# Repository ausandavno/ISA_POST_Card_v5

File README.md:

# ISA_POST_Card_v5
A plug-in diagnostic card that displays Power On Self Test (POST) codes on an 8-bit ISA data bus. Tested for use with Micro8088 and Xi8088 systems. Can be configured to listen on any address in the lower ten bits of address space. 

Current version v5.1

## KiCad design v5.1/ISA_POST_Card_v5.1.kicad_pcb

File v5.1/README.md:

# ISA_POST_Card_v5.1
Version 5.1 of a plug-in diagnostic card that displays Power On Self Test (POST) codes on an 8-bit ISA data bus. Tested for use with Micro8088 and Xi8088 systems. Can be configured to listen on any address in the lower ten bits of address space.

Board render:

Constructed board (ignore version number):

## Hardware Documentation

### Schematic and PCB Layout

[Schematics - Version 5.1 (pdf)](../v5.1/Schematics/ISA_POST_Card_v5.1-Schematic.pdf)

[PCB Layout - Version 5.1 (zip)](../v5.1/PCB_Layout/ISA_POST_Card_v5.1-PCB_Layouts.zip)

[Gerbers - Version 5.1 (zip)](../v5.1/Gerbers/ISA_POST_Card_v5.1-Gerbers.zip)

### Building Instructions

Recommend soldering components in order of height, lowest to highest: Resistors (Rx), IC sockets (if used), Resistor Networks (RNx), Capacitors (Cx), Discrete LEDs (Dx), Seven Segment LEDs (LEDx), Switches (SWx).

Recommend populating turned-pin strip headers for U2, U3, U9 and U10. Populate U2, U3 if intending to use seven-segment display driver 74LS47. Populate U9, U10 if intending to use ATF16V8B-15PU to display hexadecimal values.

### Jumpers and Switches

#### JP1 - Select chip options for U1
Position | Description
-------- | -----------
1-2 closed (default)* | Use 74x273 Series
2-3 closed | Use 74x374 Series

*Cut trace to open 1-2

#### SW1 - Lowest five bits of address space selection
Position	| Description
-------- | -----------
SW1.1 | bit 4 of address space
SW1.2 | bit 3 of address space
SW1.3 | bit 2 of address space
SW1.4 | bit 1 of address space
SW1.5 | bit 0 of address space (LSB)

#### SW2 - Highest five bits of address space selection
Position	| Description
-------- | -----------
SW2.1 | bit 9 of address space (MSB)
SW2.2 | bit 8 of address space
SW2.3 | bit 7 of address space
SW2.4 | bit 6 of address space
SW2.5 | bit 5 of address space

### Bill of Materials - v5.1

Component type     | Reference | Description            | Quantity | Possible sources and notes 
------------------ | --------- | ---------------------- | -------- | --------------------------
PCB                |           | ISA Post Card v5.1     | 1        | Use supplied Gerber or KiCad files to order from your perferred PCB fabrication house
Integrated Circuit | U1        | 74ALS273 or 74ALS374 (See JP1 Setting)   | 1        | Mouser [SN74ALS273N](https://www.mouser.com/ProductDetail/595-SN74ALS273N) or [SN74ALS374AN](https://www.mouser.com/ProductDetail/595-SN74ALS374AN)
Integrated Circuit | U2, U3    | 74LS47 (Alternative to U9, U10)   | 2        | Mouser [SN74LS47NE4](https://www.mouser.com/ProductDetail/595-SN74LS47NE4)
Integrated Circuit | U4, U5    | 74ALS521 or 74HCT688   | 2        | Mouser [SN74ALS521N](https://www.mouser.com/ProductDetail/595-SN74ALS521N) or [CD74HCT688E](https://www.mouser.com/ProductDetail/595-CD74HCT688E)
Integrated Circuit | U6, U7    | 74HCT132                | 2        | Mouser [CD74HCT132E](https://www.mouser.com/ProductDetail/595-CD74HCT132E)
Integrated Circuit | U8        | 74LS74                 | 1        | Mouser [SN74LS74AN](https://www.mouser.com/ProductDetail/595-SN74LS74AN)
Integrated Circuit | U9, U10   | ATF16V8B (Alternative to U2, U3) | 2        | Mouser [ATF16V8B-15PU](https://www.mouser.com/ProductDetail/556-AF16V8B15PU)
LED    | LED1, LED2   | 7-Segment Display W7.4mm H10mm  | 2        | Mouser [LTS-2801AG](https://www.mouser.com/ProductDetail/859-LTS-2801AG) or [LTS-2801AWC](https://www.mouser.com/ProductDetail/859-LTS-2801AWC)
LED | D1 - D4   | LED D3.0mm    | 4        | Mouser [LTL-4231N](https://www.mouser.com/ProductDetail/859-LTL-4231N)
Resistor Network   | RN1, RN2  | R_Array_SIP6 10K (Bussed)      | 2   | Mouser [4606M-101-103LF](https://www.mouser.com/ProductDetail/652-4606M-1LF-10K)
Resistor Network   | RN3 - RN6  | R_Array_SIP8 1K (Isolated)   | 4  |  Mouser [L083S122LF](https://www.mouser.com/ProductDetail/858-L083S122LF)
Resistor   | R1  | R_Axial_DIN0207 L6.3mm D2.5mm P10.16mm 10K       | 1        | Mouser [MFR-25FRF52-10K](https://www.mouser.com/ProductDetail/603-MFR-25FRF5210K)
Resistor   | R9, R13  | R_Axial_DIN0207 L6.3mm D2.5mm P10.16mm 1k | 2 | Mouser [MFR-25FRF52-1K](https://www.mouser.com/ProductDetail/MFR-25FRF52-1K)
Resistor   | R10, R14  | R_Axial_DIN0207 L6.3mm D2.5mm P10.16mm 2.4k | 2 | Mouser [MFR-25FRF52-2K4](https://www.mouser.com/ProductDetail/603-MFR-25FRF52-2K4)
Capacitor   | C1 - C8  | P5.08mm 0.1uF 50V  | 8        | Mouser [FG28X7R1H104KNT06](https://www.mouser.com/ProductDetail/810-FG28X7R1H104KNT6)
Capacitor   | C9  | P5.08mm 10uF 10V  | 1        | Mouser [FG24X7R1A106KRT06](https://www.mouser.com/ProductDetail/810-FG24X7R1A106KRT6)
Switch   | SW1, SW2  | SW_DIP_SPSTx05_Slide 9.78x14.88mm W7.62mm P2.54mm   | 2    | Mouser [CTS 206-5](https://www.mouser.com/ProductDetail/774-2065) or [C&K BD05](https://www.mouser.com/ProductDetail/611-BD05)
Socket   | for U1, U4, U5 | 20 pin 300 mil DIP socket    | 3    | Mouser [4820-3000-CP](https://www.mouser.com/ProductDetail/517-4820-3000-CP)
Socket   | for U6, U7, U8 | 14 pin 300 mil DIP socket    | 3    | Mouser [4814-3000-CP](https://www.mouser.com/ProductDetail/517-4814-3000-CP)
Socket *   | for U9, U10 | 10 WAY SIL VERT SKT           | 4    | Mouser [D01-9971042](https://www.mouser.com/ProductDetail/855-D01-9971042)
Socket *   | for U2, U3 | 8 WAY SIL VERT SKT            | 4    | Mouser [D01-9970842](https://www.mouser.com/ProductDetail/855-D01-9970842)
Socket **   | Alt for U9, U10 | 20 pin 300 mil DIP socket  | 2    | Mouser [4820-3000-CP](https://www.mouser.com/ProductDetail/517-4820-3000-CP)
Socket **   | Alt for U2, U3 | 16 pin 300 mil DIP socket   | 2    | Mouser [4816-3000-CP](https://www.mouser.com/ProductDetail/517-4816-3000-CP)

*Recommended to use SIL Sockets instead of DIP sockets if you want to swap between fitting U2, U3 and U9, U10.

**Use DIP sockets if you are comfortable committing to either U2, U3 or U9, U10. Cannot swap between chip types without removing DIP socket. 

### Alternative ICs

Supply chain distruptions have caused havoc with availability of ICs. Below are some suggestions for alternative types that are likely to work as substitues to those in the BOM. NOTE: not all alternative chip types or combinations of chip types have been tested. Use caution substituting CMOS types for Bipolar types. Bipolar outputs to CMOS inputs may give issues with voltage levels.

* 74ALS273 Alternatives:
  * Mouser [SN74LS273N](https://www.mouser.com/ProductDetail/595-SN74LS273N)
  * Mouser [SN74HCT273N](https://www.mouser.com/ProductDetail/595-SN74HCT273N)
  * Mouser [CD74ACT273E](https://www.mouser.com/ProductDetail/595-CD74ACT273E)

* 74ALS374 Alternatives:
  * Mouser [SN74LS374N](https://www.mouser.com/ProductDetail/595-SN74LS374N)
  * Mouser [SN74F374N](https://www.mouser.com/ProductDetail/595-SN74F374N)
  * Mouser [SN74HCT374N](https://www.mouser.com/ProductDetail/595-SN74HCT374N)
  * Mouser [CD74ACT374E](https://www.mouser.com/ProductDetail/595-CD74ACT374E)

* 74ALS521 Alternatives:
  * Mouser [SN74F521N](https://www.mouser.com/ProductDetail/595-SN74F521N)

* 74HCT688 Alternatives:
  * Mouser [SN74LS688N](https://www.mouser.com/ProductDetail/595-SN74LS688N)
  * Mouser [SN74ALS688N](https://www.mouser.com/ProductDetail/595-SN74ALS688N)

* 74HCT132 Alternatives:
  * Mouser [SN74LS132N](https://www.mouser.com/ProductDetail/595-SN74LS132N)

* 74LS74 Alternatives:
  * Mouser [SN74ALS74AN](https://www.mouser.com/ProductDetail/595-SN74ALS74AN)
  * Mouser [SN74F74N](https://www.mouser.com/ProductDetail/595-SN74F74N)
  * Mouser [CD74HCT74E](https://www.mouser.com/ProductDetail/595-CD74HCT74E)
  * Mouser [CD74ACT74E](https://www.mouser.com/ProductDetail/595-CD74ACT74E)

## Firmware Documentation

### ATF16V8B

The ATF16V8B-15PU chip (U9, U10) can be chosen as a substitute to the 74LS47 (U2, U3). The ATF16V8B chip is primarily used to emulate a 74LS47 seven segment display decoder IC with additional/new hex-output functionality. If one would like to be able to see hexadecimal values on the seven-segment displays of the POST card, then the ATF16V8B should be chosen.

The ATF16V8B must be programmed with a ".jed" file. A copy of this file "HEX_TO_7SEG_DECODER_COM_AN_V2.0.jed" has been placed in the "ATF16V8B_JED" folder.

Refer to my [Hex_To_Seven_Segment_Decoder](https://github.com/ausandavno/Hex_To_Seven_Segment_Decoder/tree/master/COMMON_ANODE_v2.0) repository for associated WinCUPL project files.

Refer to [My website](https://www.andavno.com/?p=672) for an overview of recent changes to the ATF16V8B program.

For some instruction on how to compile the WinCUPL code for the ATF16V8B, please see “How to Compile the Code” section of my post [7 segment display decoder with HEX output](https://www.andavno.com/?p=539).

For some instruction on how to go about programming the ATF16V8B with a TL866II PLUS programmer, please see “Flashing U16” section of my post on [building the Micro 8088](https://www.andavno.com/?p=85).

## Changes
* Version 5.1
  * First Issue

## Known Issues
* Version 5.1
  * None at present
 
## Open Hardware License
 
You may redistribute and modify this Covered Source, and make products using it, under the terms of the CERN-OHL-P v2 (https:/cern.ch/cern-ohl). This Covered Source is distributed WITHOUT ANY EXPRESS OR IMPLIED WARRANTY, INCLUDING OF MERCHANTABILITY, SATISFACTORY QUALITY AND FITNESS FOR A PARTICULAR PURPOSE. Please see the CERN-OHL-P v2 for applicable conditions.
 
Warranty Disclaimed per 5.1 of CERN-OHL-P v2.
 
Liability Excluded and Limited per 5.2 of CERN-OHL-P v2.
 
See "LICENSE_NOTICES_and_CHANGES.txt" for specific Notices relating to this hardware design.

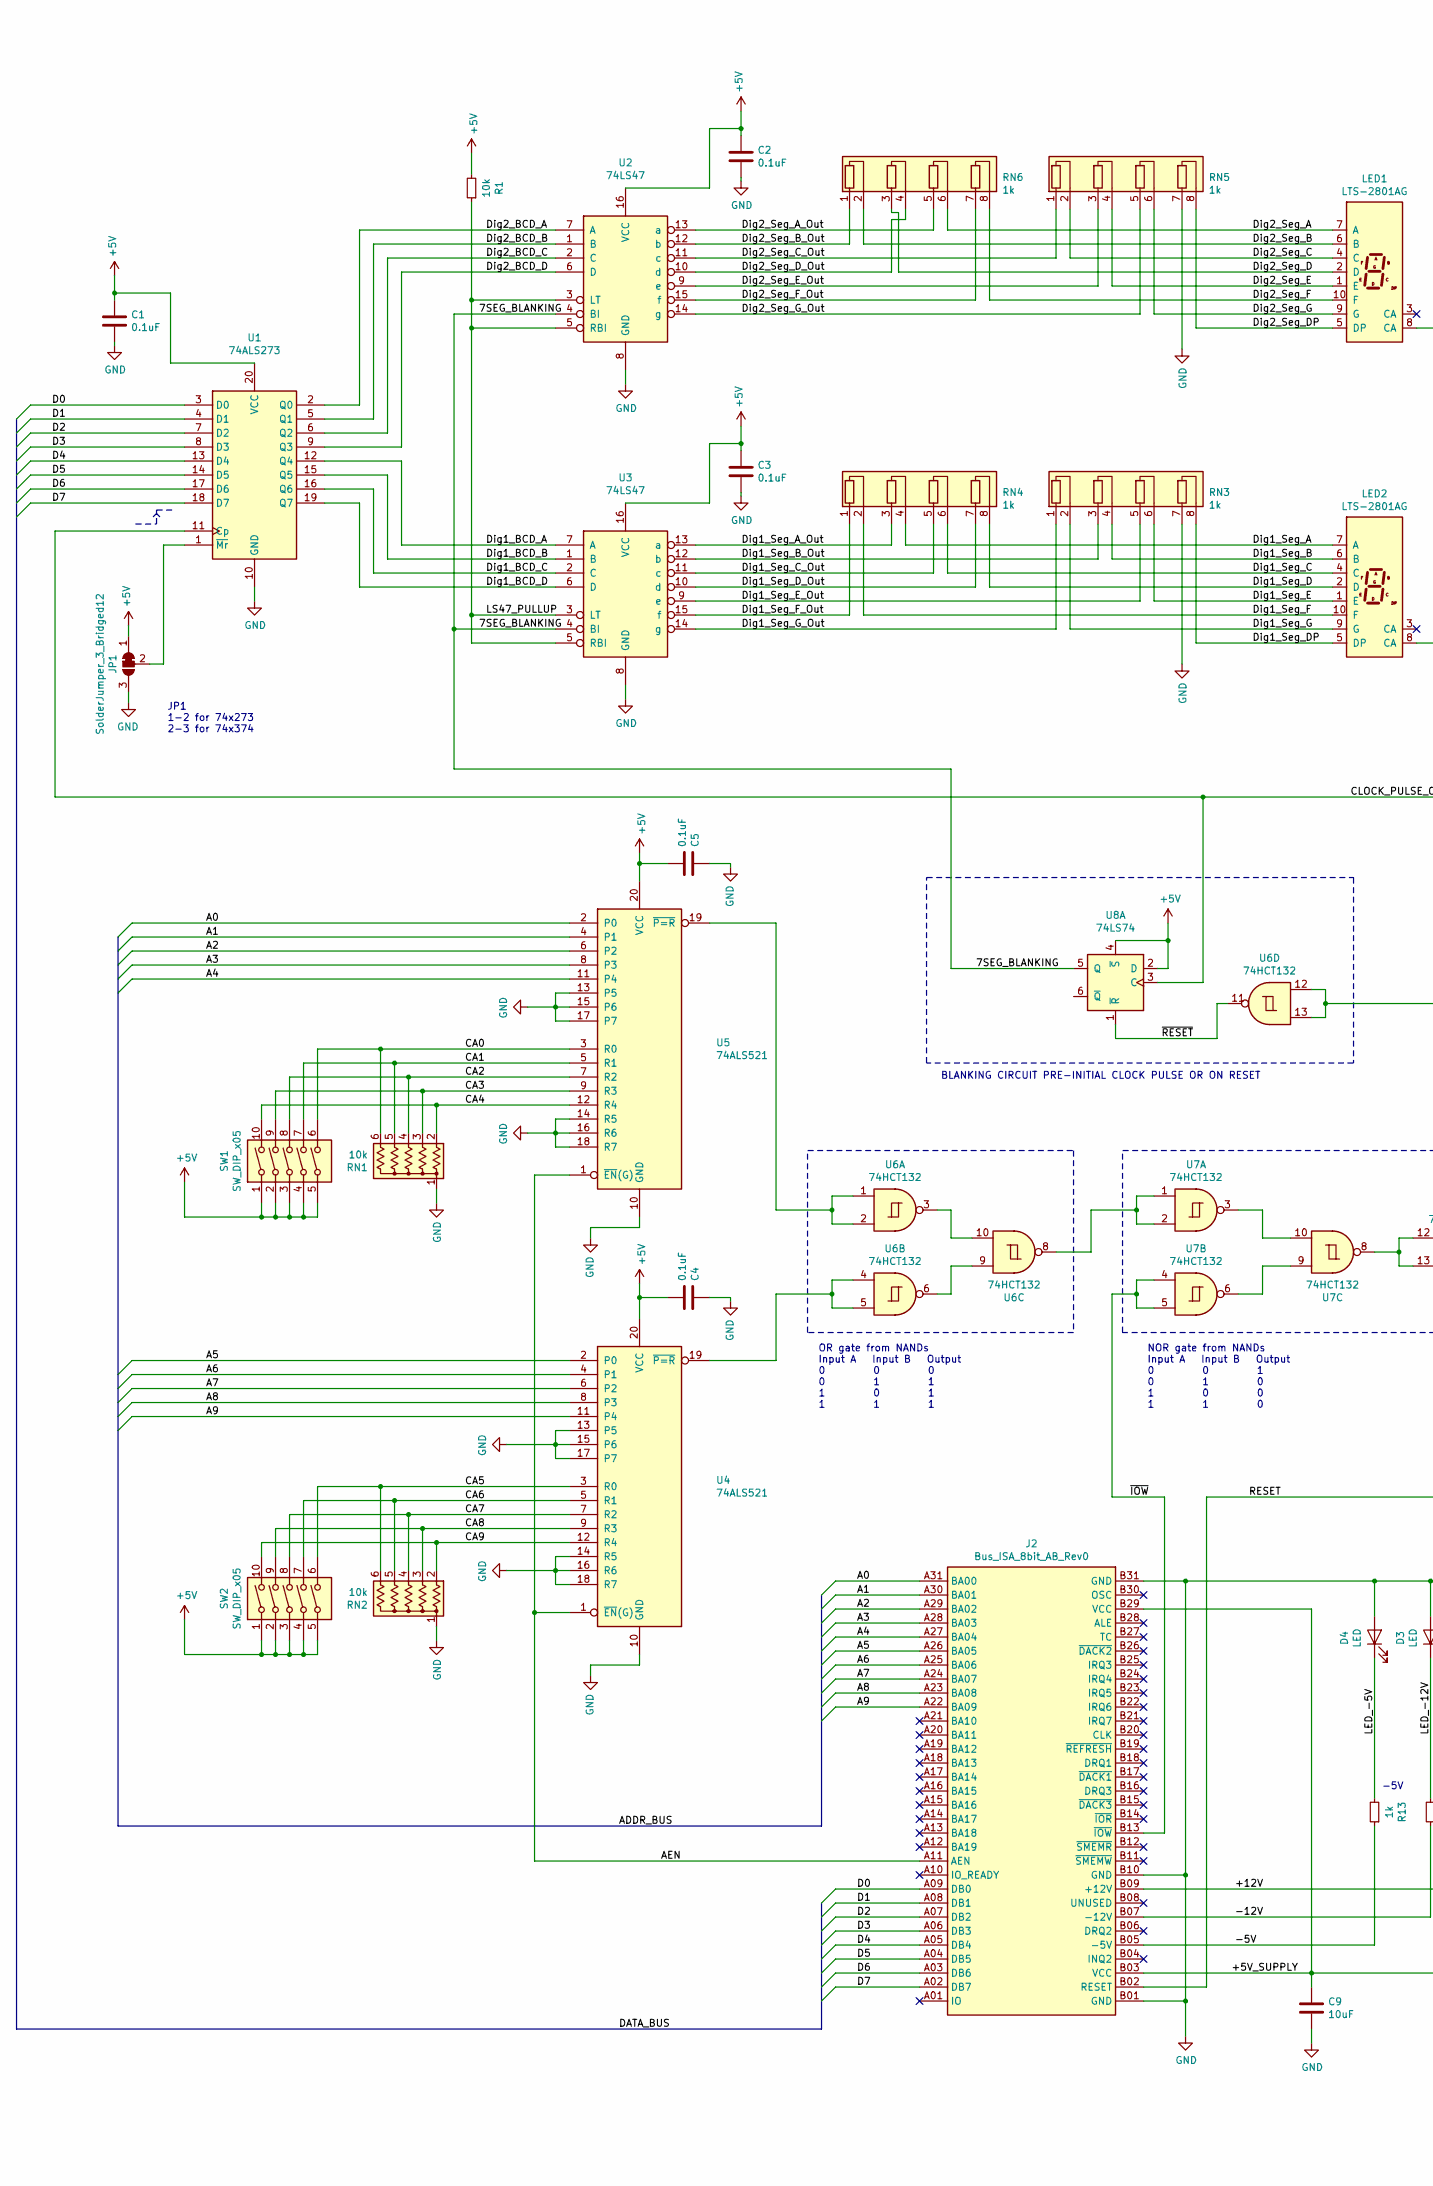
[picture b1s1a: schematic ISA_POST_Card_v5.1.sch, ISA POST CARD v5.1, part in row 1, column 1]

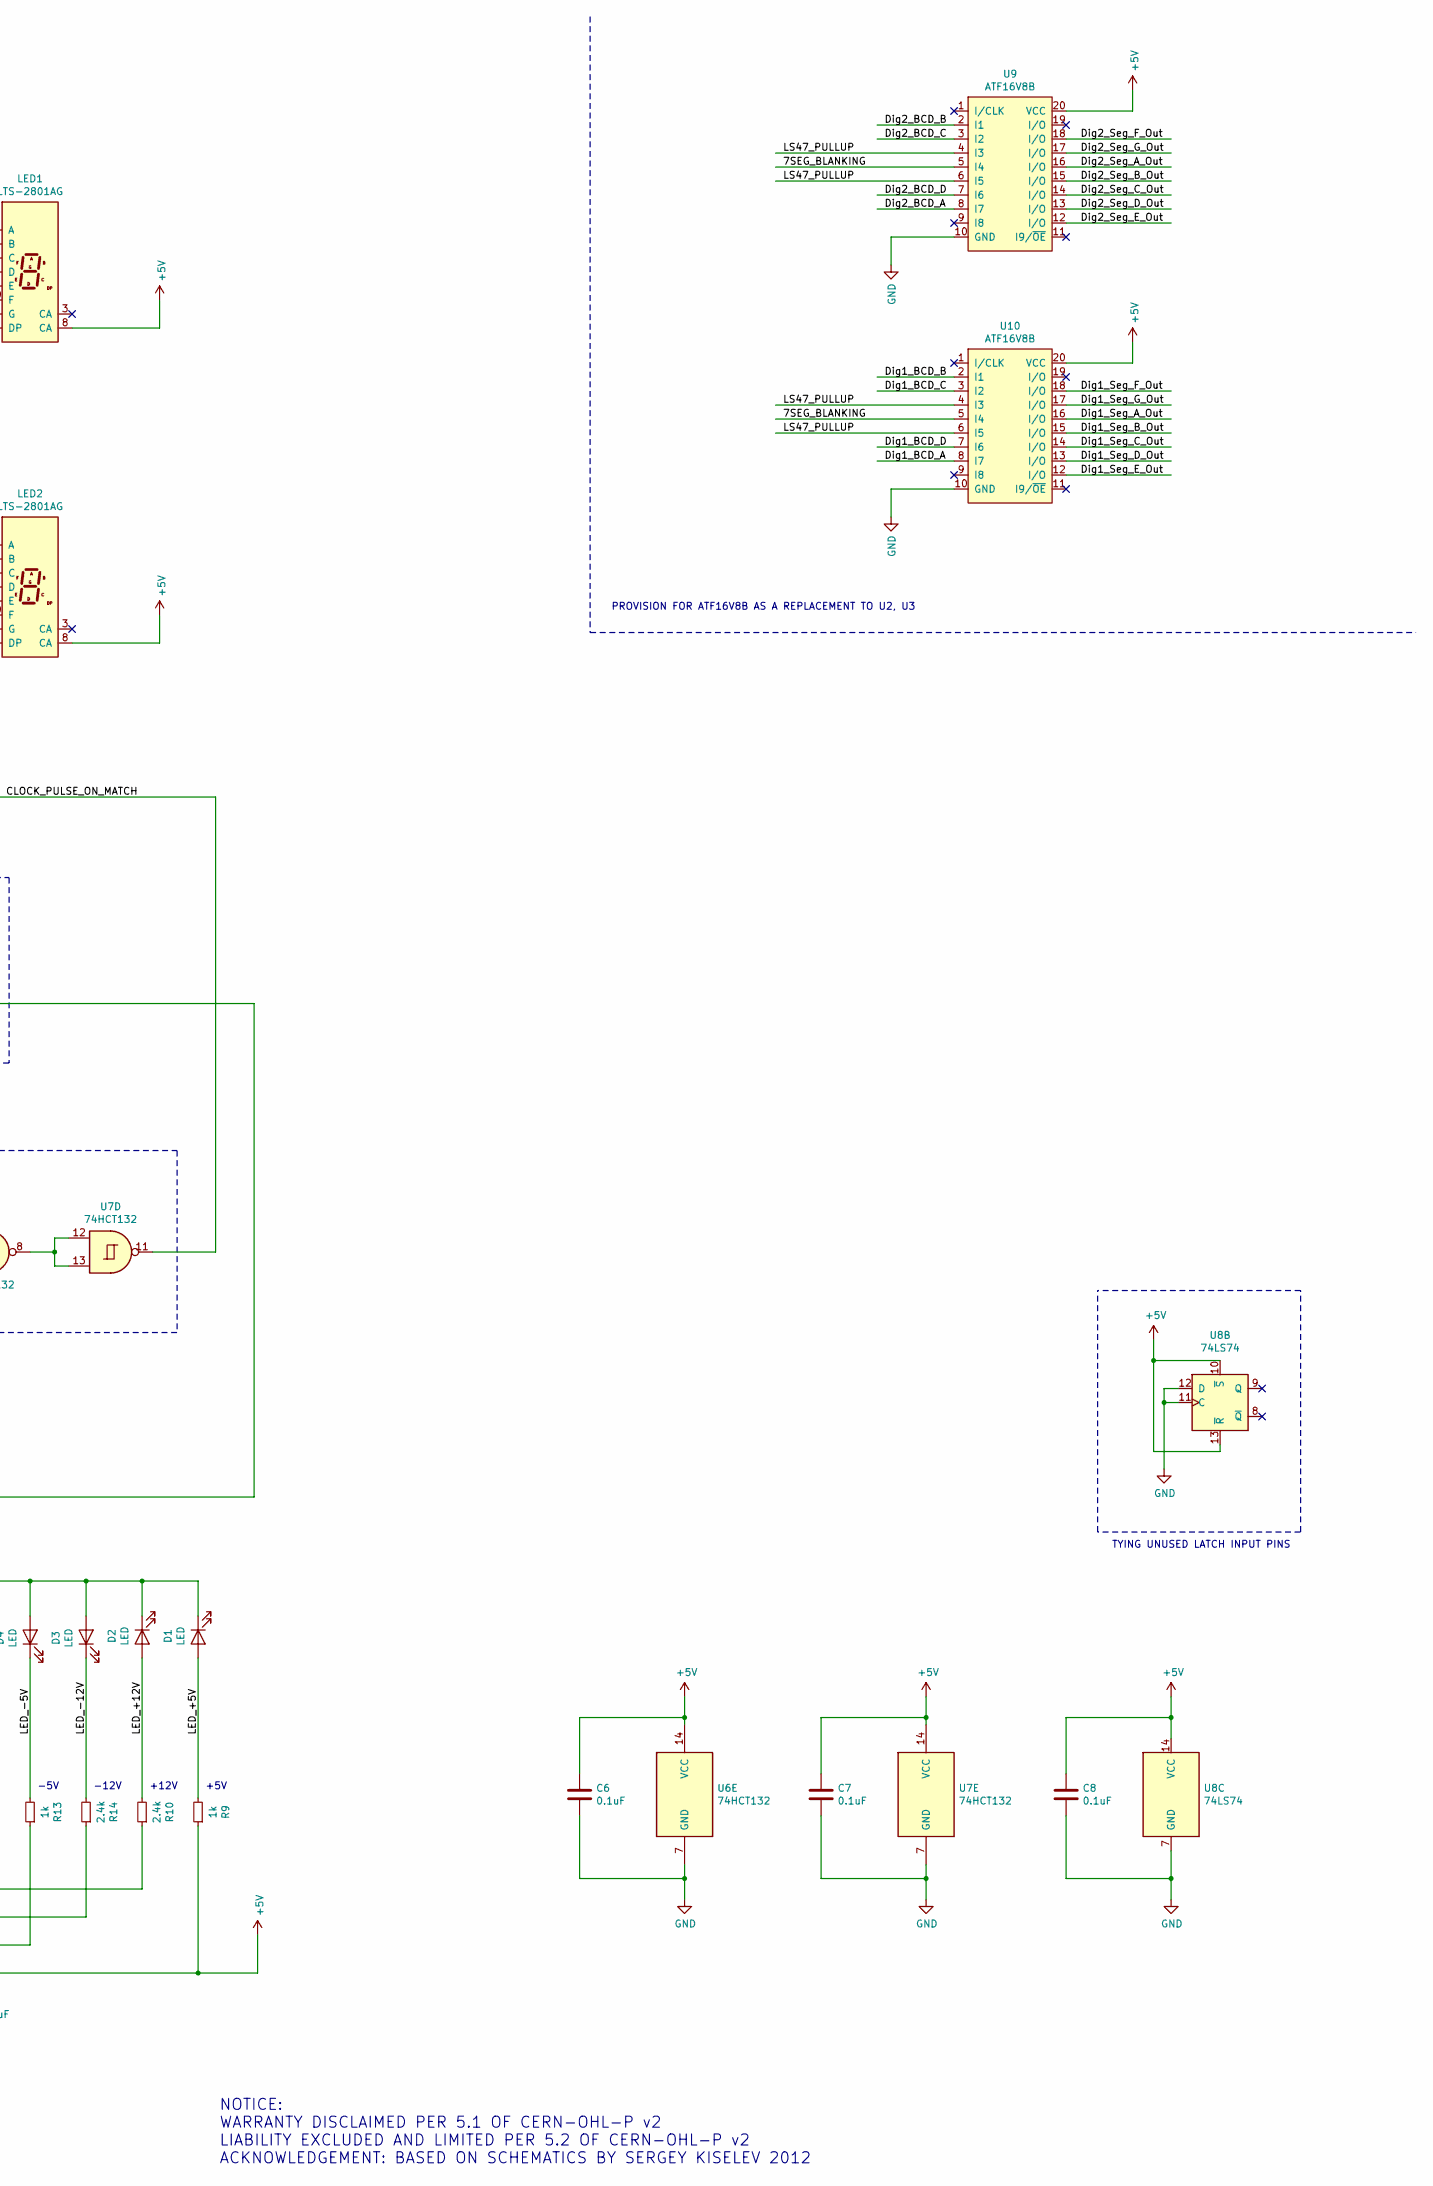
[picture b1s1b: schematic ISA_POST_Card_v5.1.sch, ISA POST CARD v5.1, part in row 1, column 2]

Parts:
C1, C2, C3, C4, C5, C6, C7, C8: 0.1uF; C_Disc_D4.3mm_W1.9mm_P5.08mm
C9: 10uF; C_Disc_D4.3mm_W1.9mm_P5.08mm
D1, D2, D3, D4: LED; LED_D3.0mm
J2: Bus_ISA_8bit_AB_Rev0; ISA_CARD_EDGE_CONNECTOR_8BIT_Rev1
JP1: SolderJumper_3_Bridged12; SolderJumper-3_P1.3mm_Bridged12_RoundedPad1.0x1.5mm_NumberL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
LED1, LED2: LTS-2801AG
R1: 10k; R_Axial_DIN0207_L6.3mm_D2.5mm_P10.16mm_Horizontal
R9, R13: 1k; R_Axial_DIN0207_L6.3mm_D2.5mm_P2.54mm_Vertical
R10, R14: 2.4k; R_Axial_DIN0207_L6.3mm_D2.5mm_P2.54mm_Vertical
RN1, RN2: 10k; R_Array_SIP6
RN3, RN4, RN5, RN6: 1k; R_Array_SIP8
SW1, SW2: SW_DIP_x05; SW_DIP_SPSTx05_Slide_9.78x14.88mm_W7.62mm_P2.54mm
U1: 74ALS273; DIP-20_W7.62mm
U2, U3: 74LS47; DIP-16_W7.62mm
U4, U5: 74ALS521; DIP-20_W7.62mm
U6, U7: 74HCT132; DIP-14_W7.62mm
U8: 74LS74; DIP-14_W7.62mm
U9, U10: ATF16V8B; DIP-20_W7.62mm

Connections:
+5V: C1.1, C2.1, C3.1, C4.2, C5.2, C6.1, C7.1, C8.1, C9.1, J2.B03 (VCC), J2.B29 (VCC), JP1.1 (A), LED1.8 (CA), LED2.8 (CA), R1.2, R9.1, SW1.1, SW1.2, SW1.3, SW1.4, SW1.5, SW2.1, SW2.2, SW2.3, SW2.4, SW2.5, U1.20 (VCC), U2.16 (VCC), U3.16 (VCC), U4.20 (VCC), U5.20 (VCC), U6.14 (VCC), U7.14 (VCC), U8.2 (D), U8.4 (~S), U8.10 (~S), U8.13 (~R), U8.14 (VCC), U9.20 (VCC), U10.20 (VCC)
/7SEG_BLANKING: U2.4 (BI), U3.4 (BI), U8.5 (Q), U9.5 (I4), U10.5 (I4)
/+12V: J2.B09 (+12V), R10.1
/-5V: J2.B05 (-5V), R13.1
/-12V: J2.B07 (-12V), R14.1
/A0: J2.A31 (BA00), U5.2 (P0)
/A1: J2.A30 (BA01), U5.4 (P1)
/A2: J2.A29 (BA02), U5.6 (P2)
/A3: J2.A28 (BA03), U5.8 (P3)
/A4: J2.A27 (BA04), U5.11 (P4)
/A5: J2.A26 (BA05), U4.2 (P0)
/A6: J2.A25 (BA06), U4.4 (P1)
/A7: J2.A24 (BA07), U4.6 (P2)
/A8: J2.A23 (BA08), U4.8 (P3)
/A9: J2.A22 (BA09), U4.11 (P4)
/AEN: J2.A11 (AEN), U4.1 (~EN~(G)), U5.1 (~EN~(G))
/CA0: RN1.6 (R5), SW1.6, U5.3 (R0)
/CA1: RN1.5 (R4), SW1.7, U5.5 (R1)
/CA2: RN1.4 (R3), SW1.8, U5.7 (R2)
/CA3: RN1.3 (R2), SW1.9, U5.9 (R3)
/CA4: RN1.2 (R1), SW1.10, U5.12 (R4)
/CA5: RN2.6 (R5), SW2.6, U4.3 (R0)
/CA6: RN2.5 (R4), SW2.7, U4.5 (R1)
/CA7: RN2.4 (R3), SW2.8, U4.7 (R2)
/CA8: RN2.3 (R2), SW2.9, U4.9 (R3)
/CA9: RN2.2 (R1), SW2.10, U4.12 (R4)
/CLOCK_PULSE_ON_MATCH: U1.11 (Cp), U7.11, U8.3 (C)
/D0: J2.A09 (DB0), U1.3 (D0)
/D1: J2.A08 (DB1), U1.4 (D1)
/D2: J2.A07 (DB2), U1.7 (D2)
/D3: J2.A06 (DB3), U1.8 (D3)
/D4: J2.A05 (DB4), U1.13 (D4)
/D5: J2.A04 (DB5), U1.14 (D5)
/D6: J2.A03 (DB6), U1.17 (D6)
/D7: J2.A02 (DB7), U1.18 (D7)
/Dig1_BCD_A: U1.12 (Q4), U3.7 (A), U10.8 (I7)
/Dig1_BCD_B: U1.15 (Q5), U3.1 (B), U10.2 (I1)
/Dig1_BCD_C: U1.16 (Q6), U3.2 (C), U10.3 (I2)
/Dig1_BCD_D: U1.19 (Q7), U3.6 (D), U10.7 (I6)
/Dig1_Seg_A: LED2.7 (A), RN4.4 (R2.2)
/Dig1_Seg_A_Out: RN4.3 (R2.1), U3.13 (a), U10.16 (I/O)
/Dig1_Seg_B: LED2.6 (B), RN3.4 (R2.2)
/Dig1_Seg_B_Out: RN3.3 (R2.1), U3.12 (b), U10.15 (I/O)
/Dig1_Seg_C: LED2.4 (C), RN4.6 (R3.2)
/Dig1_Seg_C_Out: RN4.5 (R3.1), U3.11 (c), U10.14 (I/O)
/Dig1_Seg_D: LED2.2 (D), RN4.8 (R4.2)
/Dig1_Seg_DP: LED2.5 (DP), RN3.8 (R4.2)
/Dig1_Seg_D_Out: RN4.7 (R4.1), U3.10 (d), U10.13 (I/O)
/Dig1_Seg_E: LED2.1 (E), RN3.6 (R3.2)
/Dig1_Seg_E_Out: RN3.5 (R3.1), U3.9 (e), U10.12 (I/O)
/Dig1_Seg_F: LED2.10 (F), RN4.2 (R1.2)
/Dig1_Seg_F_Out: RN4.1 (R1.1), U3.15 (f), U10.18 (I/O)
/Dig1_Seg_G: LED2.9 (G), RN3.2 (R1.2)
/Dig1_Seg_G_Out: RN3.1 (R1.1), U3.14 (g), U10.17 (I/O)
/Dig2_BCD_A: U1.2 (Q0), U2.7 (A), U9.8 (I7)
/Dig2_BCD_B: U1.5 (Q1), U2.1 (B), U9.2 (I1)
/Dig2_BCD_C: U1.6 (Q2), U2.2 (C), U9.3 (I2)
/Dig2_BCD_D: U1.9 (Q3), U2.6 (D), U9.7 (I6)
/Dig2_Seg_A: LED1.7 (A), RN6.6 (R3.2)
/Dig2_Seg_A_Out: RN6.5 (R3.1), U2.13 (a), U9.16 (I/O)
/Dig2_Seg_B: LED1.6 (B), RN6.2 (R1.2)
/Dig2_Seg_B_Out: RN6.1 (R1.1), U2.12 (b), U9.15 (I/O)
/Dig2_Seg_C: LED1.4 (C), RN5.2 (R1.2)
/Dig2_Seg_C_Out: RN5.1 (R1.1), U2.11 (c), U9.14 (I/O)
/Dig2_Seg_D: LED1.2 (D), RN6.3 (R2.1)
/Dig2_Seg_DP: LED1.5 (DP), RN5.8 (R4.2)
/Dig2_Seg_D_Out: RN6.4 (R2.2), U2.10 (d), U9.13 (I/O)
/Dig2_Seg_E: LED1.1 (E), RN5.4 (R2.2)
/Dig2_Seg_E_Out: RN5.3 (R2.1), U2.9 (e), U9.12 (I/O)
/Dig2_Seg_F: LED1.10 (F), RN6.8 (R4.2)
/Dig2_Seg_F_Out: RN6.7 (R4.1), U2.15 (f), U9.18 (I/O)
/Dig2_Seg_G: LED1.9 (G), RN5.6 (R3.2)
/Dig2_Seg_G_Out: RN5.5 (R3.1), U2.14 (g), U9.17 (I/O)
/LED_+5V: D1.2 (A), R9.2
/LED_+12V: D2.2 (A), R10.2
/LED_-5V: D4.1 (K), R13.2
/LED_-12V: D3.1 (K), R14.2
/LS47_PULLUP: R1.1, U2.3 (LT), U2.5 (RBI), U3.3 (LT), U3.5 (RBI), U9.4 (I3), U9.6 (I5), U10.4 (I3), U10.6 (I5)
/RESET: J2.B02 (RESET), U6.12, U6.13
/~IOW~: J2.B13 (~IOW), U7.4, U7.5
/~RESET~: U6.11, U8.1 (~R)
GND: C1.2, C2.2, C3.2, C4.1, C5.1, C6.2, C7.2, C8.2, C9.2, D1.1 (K), D2.1 (K), D3.2 (A), D4.2 (A), J2.B01 (GND), J2.B10 (GND), J2.B31 (GND), JP1.3 (B), RN1.1 (common), RN2.1 (common), RN3.7 (R4.1), RN5.7 (R4.1), U1.10 (GND), U2.8 (GND), U3.8 (GND), U4.10 (GND), U4.13 (P5), U4.14 (R5), U4.15 (P6), U4.16 (R6), U4.17 (P7), U4.18 (R7), U5.10 (GND), U5.13 (P5), U5.14 (R5), U5.15 (P6), U5.16 (R6), U5.17 (P7), U5.18 (R7), U6.7 (GND), U7.7 (GND), U8.7 (GND), U8.11 (C), U8.12 (D), U9.10 (GND), U10.10 (GND)
unnamed: JP1.2 (C), U1.1 (~Mr)
unnamed: U4.19 (~P=R~), U6.4, U6.5
unnamed: U5.19 (~P=R~), U6.1, U6.2
unnamed: U6.6, U6.9
unnamed: U6.8, U7.1, U7.2
unnamed: U6.3, U6.10
unnamed: U7.6, U7.9
unnamed: U7.3, U7.10
unnamed: U7.8, U7.12, U7.13

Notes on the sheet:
PROVISION FOR ATF16V8B AS A REPLACEMENT TO U2, U3
-5V
-12V
+5V
+12V
OR gate from NANDs Input A Input B Output 0 0 0 0 1 1 1 0 1 1 1 1
NOR gate from NANDs Input A Input B Output 0 0 1 0 1 0 1 0 0 1 1 0
JP1 1-2 for 74x273 2-3 for 74x374
BLANKING CIRCUIT PRE-INITIAL CLOCK PULSE OR ON RESET
TYING UNUSED LATCH INPUT PINS
NOTICE: WARRANTY DISCLAIMED PER 5.1 OF CERN-OHL-P v2 LIABILITY EXCLUDED AND LIMITED PER 5.2 OF CERN-OHL-P v2 ACKNOWLEDGEMENT: BASED ON SCHEMATICS BY SERGEY KISELEV 2012

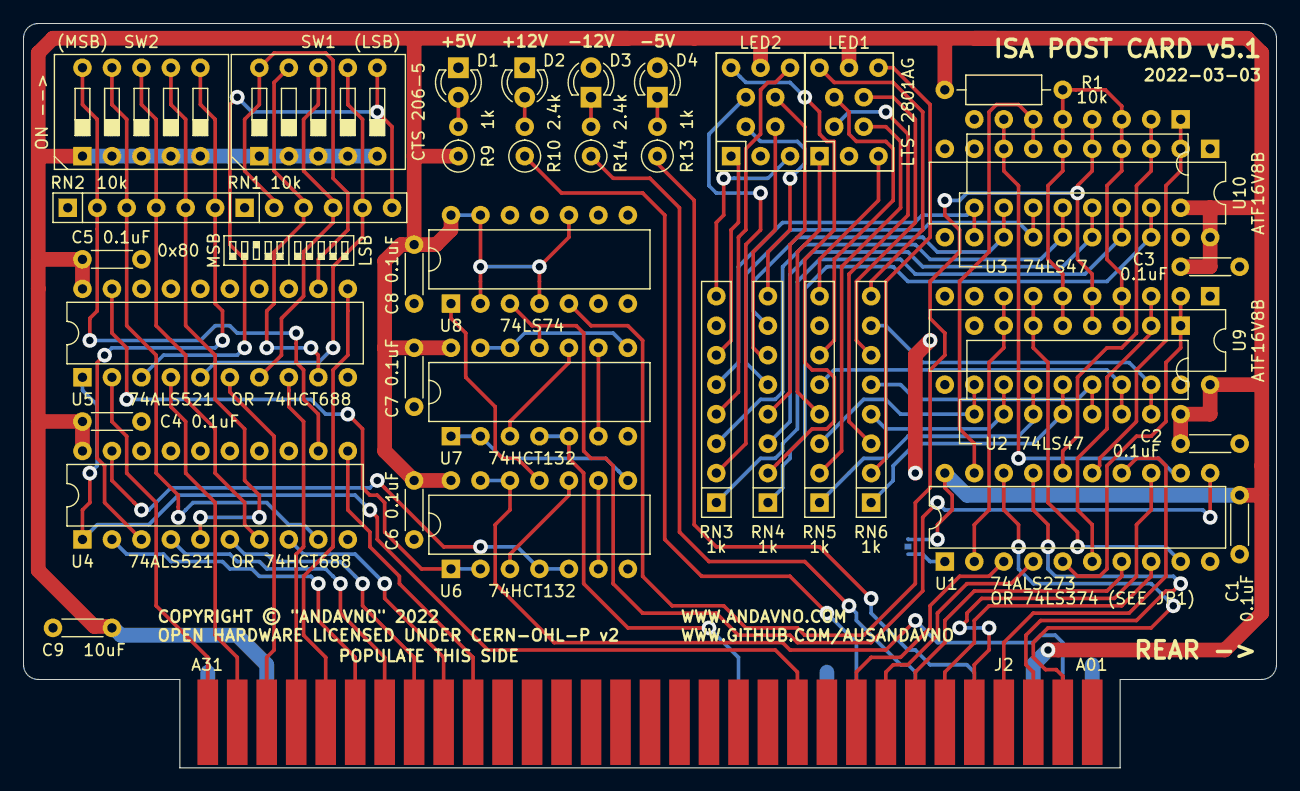
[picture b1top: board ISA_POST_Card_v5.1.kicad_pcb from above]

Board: 2 copper layers, 108.0 x 64.1 mm, 40 parts (1 on the bottom side), 91 nets.

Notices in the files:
v5.1/README.md:
Open Hardware License:
You may redistribute and modify this Covered Source, and make products using it, under the terms of the CERN-OHL-P v2 (https:/cern.ch/cern-ohl). This Covered Source is distributed WITHOUT ANY EXPRESS OR IMPLIED WARRANTY, INCLUDING OF MERCHANTABILITY, SATISFACTORY QUALITY AND FITNESS FOR A PARTICULAR PURPOSE. Please see the CERN-OHL-P v2 for applicable conditions.
See "LICENSE_NOTICES_and_CHANGES.txt" for specific Notices relating to this hardware design.
v5.1/ISA_POST_Card_v5.1.kicad_pcb:
COPYRIGHT © \"ANDAVNO\" 2022
